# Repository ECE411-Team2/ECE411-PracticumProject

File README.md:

# ECE-411-Team-2

Our project planning will be split into practium checkpoints, each with their own focus:
  1. Teams Formed 
  2. Projects Decided 
  3. Project requirements (Product Design Specification - PDS)
  4. Preliminary schematic
  5. Final schematic + preliminary layout
  6. Boards to manufacturing (actual final schematic + final layout)
  7. Demonstrations

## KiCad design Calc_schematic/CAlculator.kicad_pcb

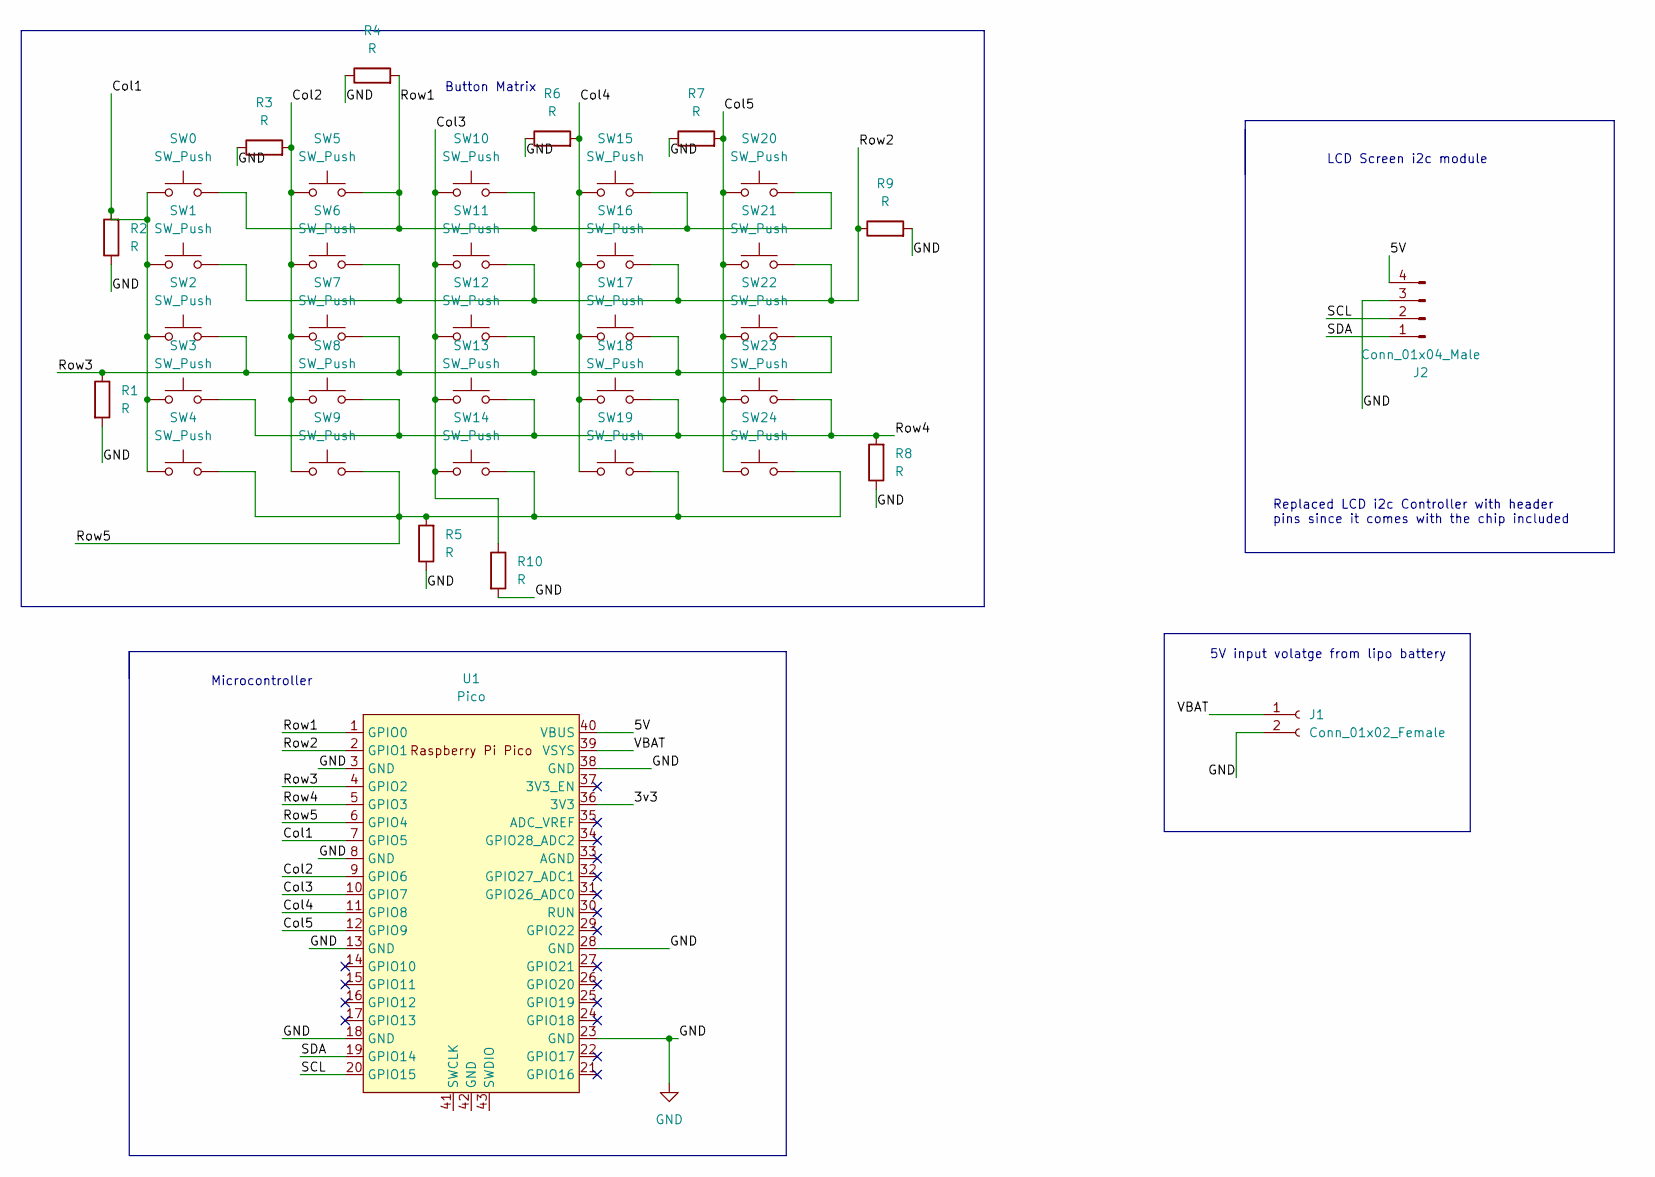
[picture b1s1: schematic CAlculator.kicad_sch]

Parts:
J1: Conn_01x02_Female; JST_PH_B2B-PH-K_1x02_P2.00mm_Vertical
J2: Conn_01x04_Male; PinHeader_1x04_P2.54mm_Vertical
R1, R2, R3, R4, R5, R6, R7, R8, R9, R10: R; RESC3216X60N
SW0, SW1, SW2, SW3, SW4, SW5, SW6, SW7, SW8, SW9, SW10, SW11, SW12, SW13, SW14, SW15, SW16, SW17, SW18, SW19, SW20, SW21, SW22, SW23, SW24: SW_Push; SW_PUSH_6mm_H5mm
U1: Pico; RPi_Pico_SMD_TH

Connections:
/3v3: U1.36 (3V3)
/5V: J2.4, U1.40 (VBUS)
/Col1: R2.2, SW0.1, SW1.1, SW2.1, SW3.1, SW4.1, U1.7 (GPIO5)
/Col2: R3.2, SW5.1, SW6.1, SW7.1, SW8.1, SW9.1, U1.9 (GPIO6)
/Col3: R10.1, SW10.1, SW11.1, SW12.1, SW13.1, SW14.1, U1.10 (GPIO7)
/Col4: R6.2, SW15.1, SW16.1, SW17.1, SW18.1, SW19.1, U1.11 (GPIO8)
/Col5: R7.2, SW20.1, SW21.1, SW22.1, SW23.1, SW24.1, U1.12 (GPIO9)
/Row1: R4.2, SW0.2, SW5.2, SW10.2, SW15.2, SW20.2, U1.1 (GPIO0)
/Row2: R9.1, SW1.2, SW6.2, SW11.2, SW16.2, SW21.2, U1.2 (GPIO1)
/Row3: R1.1, SW2.2, SW7.2, SW12.2, SW17.2, SW22.2, U1.4 (GPIO2)
/Row4: R8.2, SW3.2, SW8.2, SW13.2, SW18.2, SW23.2, U1.5 (GPIO3)
/Row5: R5.2, SW4.2, SW9.2, SW14.2, SW19.2, SW24.2, U1.6 (GPIO4)
/SCL: J2.2, U1.20 (GPIO15)
/SDA: J2.1, U1.19 (GPIO14)
/VBAT: J1.1, U1.39 (VSYS)
GND: J1.2, J2.3, R1.2, R2.1, R3.1, R4.1, R5.1, R6.1, R7.1, R8.1, R9.2, R10.2, U1.3 (GND), U1.8 (GND), U1.13 (GND), U1.18 (GND), U1.23 (GND), U1.28 (GND), U1.38 (GND)

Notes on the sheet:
LCD Screen i2c module
5V input volatge from lipo battery
Microcontroller
Replaced LCD i2c Controller with header pins since it comes with the chip included
Button Matrix

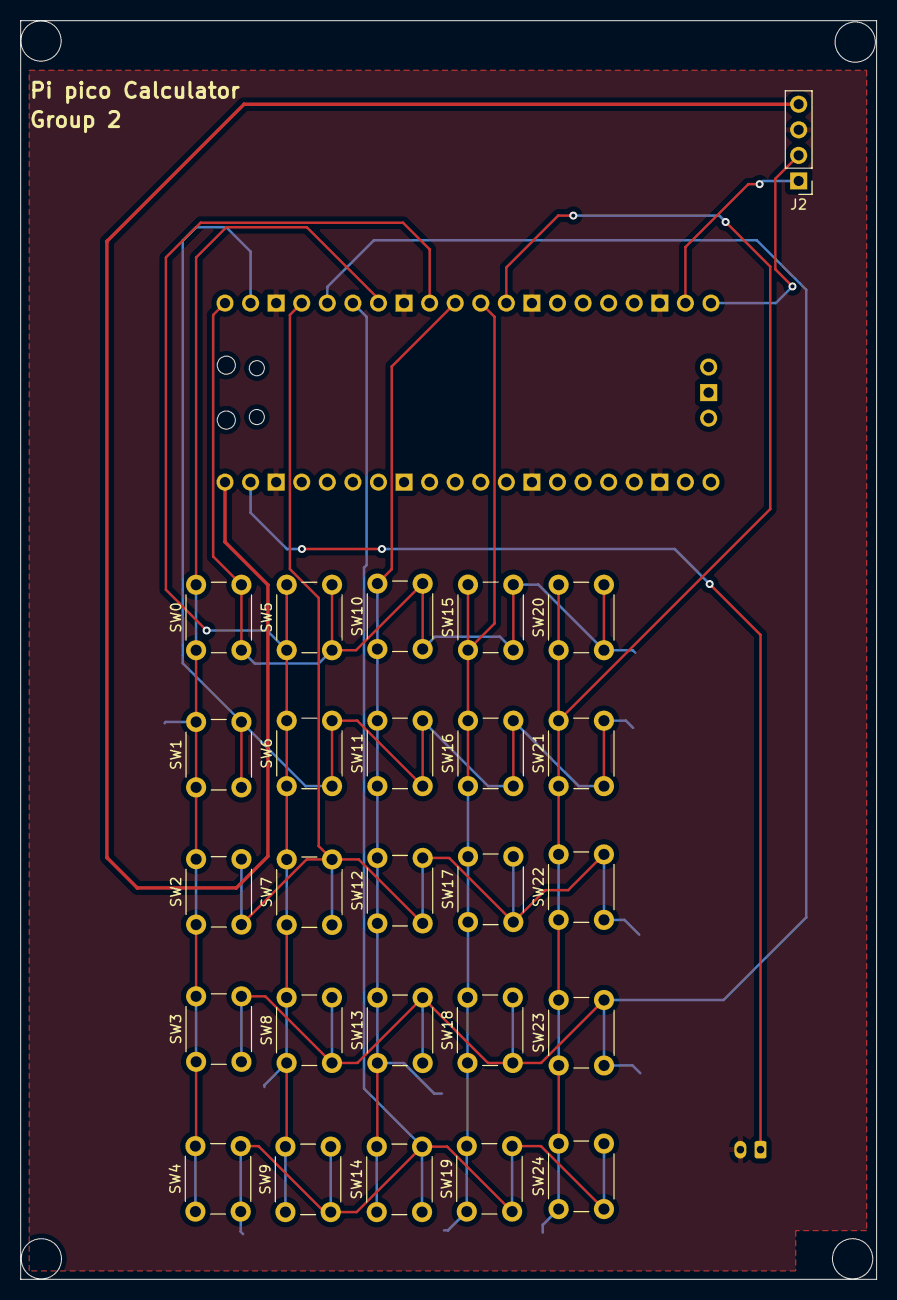
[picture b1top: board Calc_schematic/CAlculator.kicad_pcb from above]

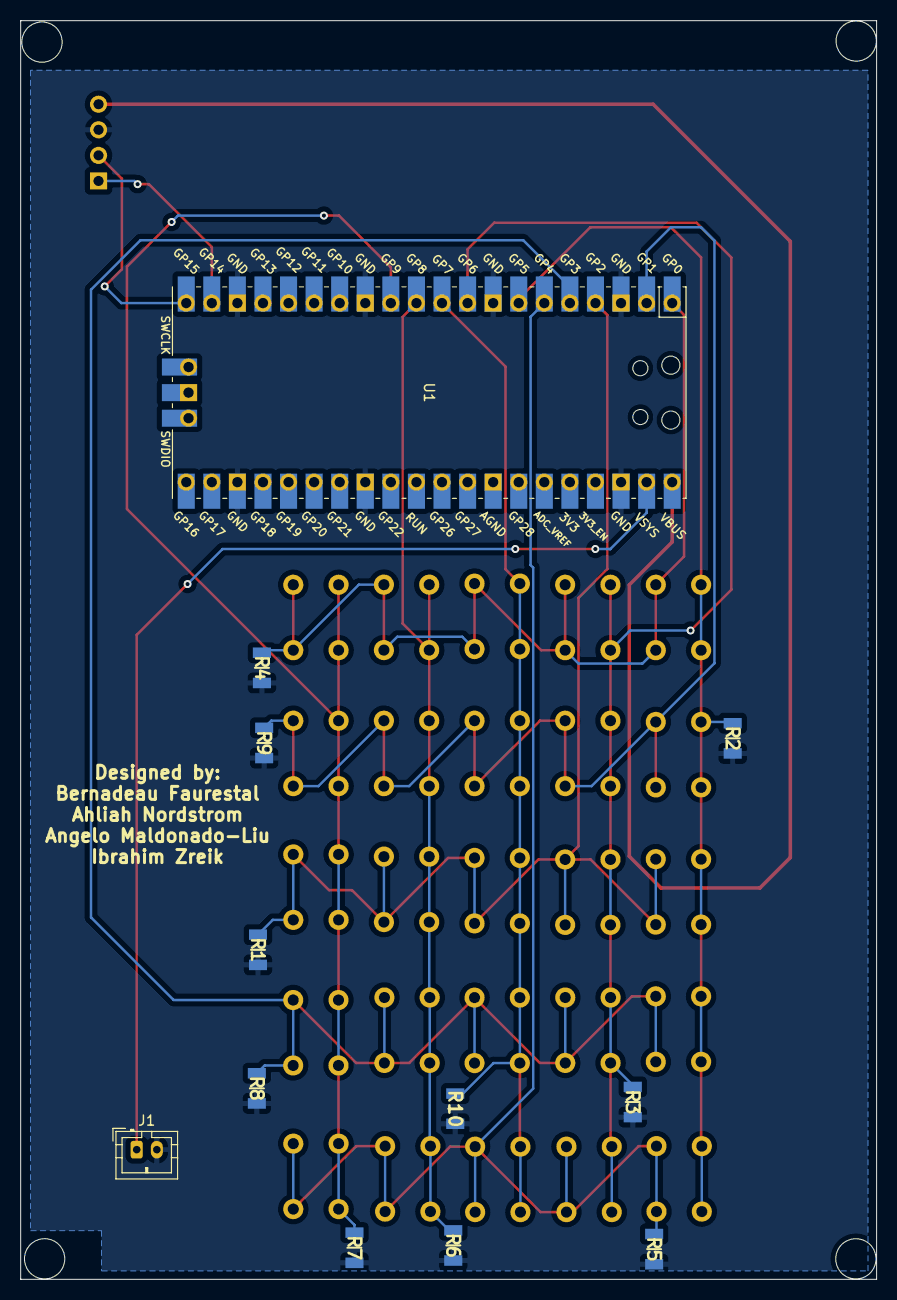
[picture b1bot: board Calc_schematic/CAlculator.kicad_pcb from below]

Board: 2 copper layers, 85.0 x 125.0 mm, 38 parts (12 on the bottom side), 15 nets.

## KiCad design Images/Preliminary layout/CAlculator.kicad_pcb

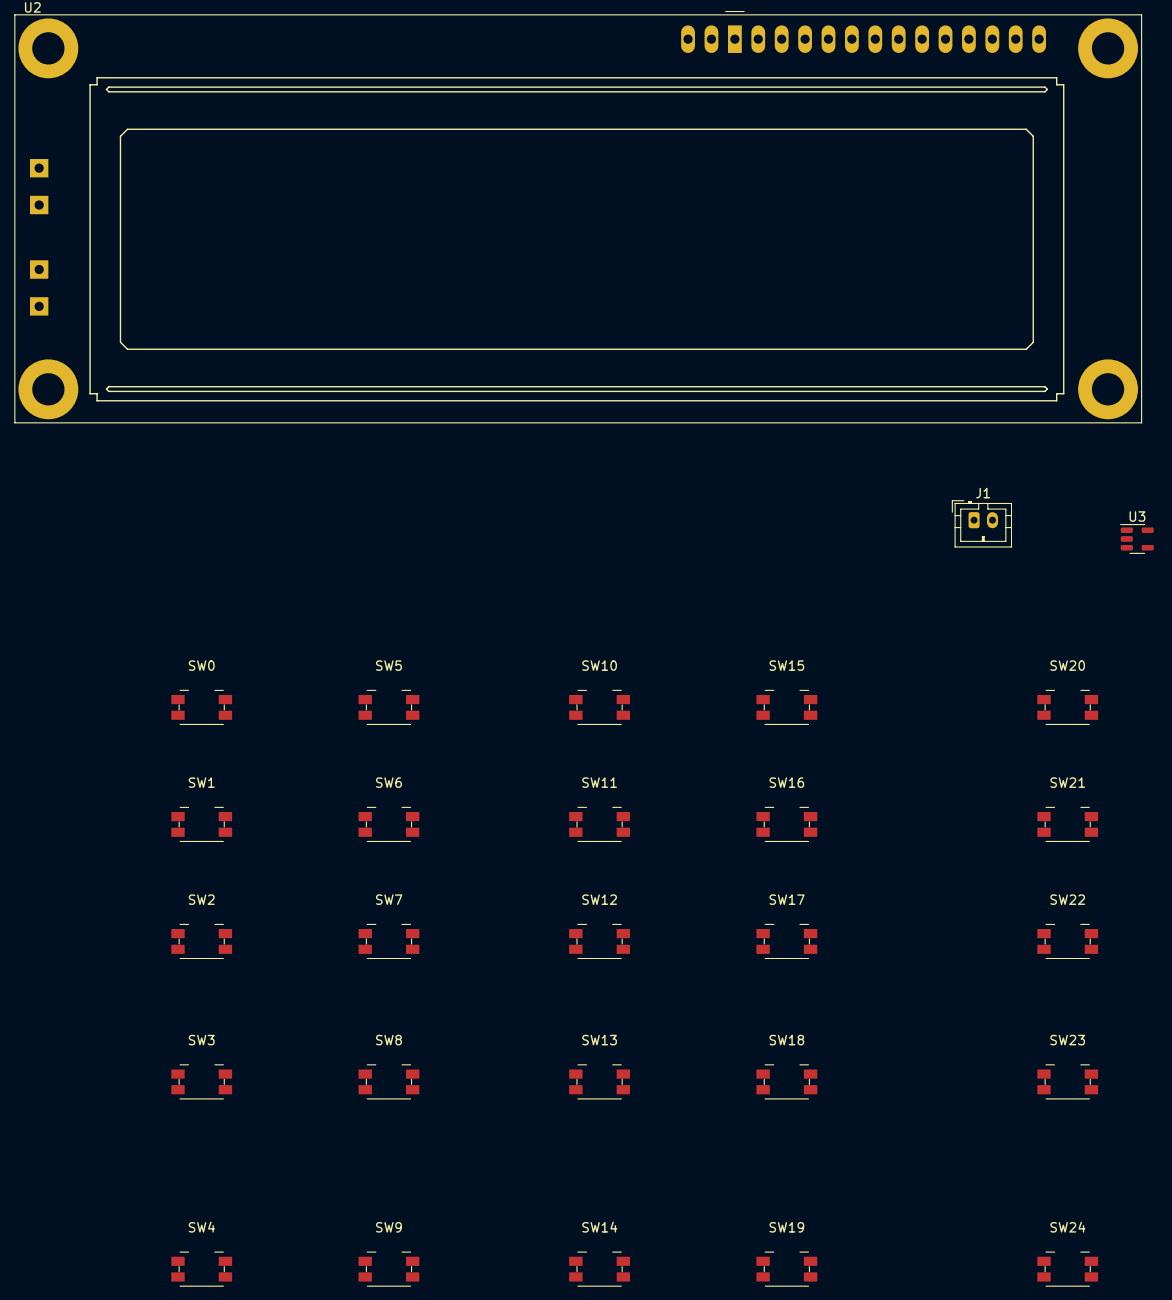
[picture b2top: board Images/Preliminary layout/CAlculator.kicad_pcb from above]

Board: 2 copper layers, 28 parts (0 on the bottom side), 10 nets, no tracks yet.

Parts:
J1: Conn_01x02_Female; JST_PH_B2B-PH-K_1x02_P2.00mm_Vertical
SW0, SW1, SW2, SW3, SW4, SW5, SW6, SW7, SW8, SW9, SW10, SW11, SW12, SW13, SW14, SW15, SW16, SW17, SW18, SW19, SW20, SW21, SW22, SW23, SW24: SW_Push; Panasonic_EVQPUK_EVQPUB
U2: LCD-016N002L
U3: AP2112K-3.3; SOT-23-5

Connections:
unnamed: SW0.1, SW1.1, SW2.1, SW3.1, SW4.1
unnamed: SW0.2, SW5.2, SW10.2, SW15.2, SW20.2
unnamed: SW1.2, SW6.2, SW11.2, SW16.2, SW21.2
unnamed: SW5.1, SW6.1, SW7.1, SW8.1, SW9.1
unnamed: SW10.1, SW11.1, SW12.1, SW13.1, SW14.1
unnamed: SW2.2, SW7.2, SW12.2, SW17.2, SW22.2
unnamed: SW3.2, SW8.2, SW13.2, SW18.2, SW23.2
unnamed: SW4.2, SW9.2, SW14.2, SW19.2, SW24.2
unnamed: SW15.1, SW16.1, SW17.1, SW18.1, SW19.1
unnamed: SW20.1, SW21.1, SW22.1, SW23.1, SW24.1

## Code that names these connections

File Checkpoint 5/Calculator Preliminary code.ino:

//Written by Angelo Maldonado-Liu
//10/28/2022
//PSU ECE 411
//
//
//
/* To do:
      assign values to each row/column pair
      for the equals sign, add in an LCD clear and then output the answer.
      Hex to Binary to Decimal converter.
      need to decide if i have say, 10 in the buffer, when I hit the convert button, does it become 0b1010, and then become 0xA, because if so, then I need to change the size of acceptable values, so that I can fit a D, B, H symbol to signify what type of values we are getting.
      */



#include <Wire.h>
#include <LiquidCrystal_I2C.h>

int row1 = ;
int row2 = ;
int row3 = ;
int row4 = ;
int row5 = ;
int col1 = ;
int col2 = ;
int col3 = ;
int col4 = ;
int col5 = ;

LiquidCrystal_I2C lcd(FIND THE LCD DISPLAY ADDRESS,20,4);  // set the LCD address to blank for a 20 chars and 4 line display (need to determine for our LCD)


char charOutput;
//variables needed for the math, max of 20 digits
char operation = '0';
char value0[18];
char value1[18];
char result[20];
int numType = 0;



int val# = 0;
int numCount;

//trash variable to hold things use with strtoul https://www.tutorialspoint.com/c_standard_library/c_function_strtoul.htm
char *garbage;

void setup() {
  Serial.begin(9600);
  // put your setup code here, to run once:
  //Here we put the button array gpio ports
  lcd.init();                      // initialize the lcd 
  lcd.init();
  // Print a message to the LCD.
  lcd.backlight();
  lcd.setCursor(1,0);




  //variables

}

void loop() {
  // put your main code here, to run repeatedly:
  
  //LCD gpio ports
  pinMode(row1, OUTPUT);
  pinMode(row2, OUTPUT);
  pinMode(row3, OUTPUT);
  pinMode(row4, OUTPUT);
  pinMode(row5, OUTPUT);
  pinMode(col1, INPUT);
  pinMode(col2, INPUT);
  pinMode(col3, INPUT);
  pinMode(col4, INPUT);
  pinMode(col5, INPUT);

  haveInput = 0;
  delay(50);
  if(val# == 1)
  {
    lcd.setCursor(2,1);
  }
  else
  {
    lcd.setCursor(1,0);
  }
  //check which button
  while(haveInput == 0)
  {
    if(digitalRead(col1) == 1)
    {
      //change ROWS and COLUMNS 
      switchIO();

      if(digitalRead(row1) == 1)
      {
        charOutput = ;
      }
      else if(digitalRead(row2) == 1)
      {
        charOutput = ;
      }
      else if(digitalRead(row3) == 1)
      {
        charOutput = ;
      }
      else if(digitalRead(row4) == 1)
      {
        charOutput = ;
      }
      else if(digitalRead(row5) == 1)
      {
        charOutput = ;
      }
      haveInput = 1;
    }
    if(digitalRead(col2) == 1)
    {
      //change ROWS and COLUMNS 
      switchIO();

      if(digitalRead(row1) == 1)
      {
        charOutput = ;
      }
      else if(digitalRead(row2) == 1)
      {
        charOutput = ;
      }
      else if(digitalRead(row3) == 1)
      {
        charOutput = ;
      }
      else if(digitalRead(row4) == 1)
      {
        charOutput = ;
      }
      else if(digitalRead(row5) == 1)
      {
        charOutput = ;
      }
      haveInput = 1;
    }

    if(digitalRead(col3) == 1)
    {
      //change ROWS and COLUMNS 
      switchIO();

      if(digitalRead(row1) == 1)
      {
        charOutput = ;
      }
      else if(digitalRead(row2) == 1)
      {
        charOutput = ;
      }
      else if(digitalRead(row3) == 1)
      {
        charOutput = ;
      }
      else if(digitalRead(row4) == 1)
      {
        charOutput = ;
      }
      else if(digitalRead(row5) == 1)
      {
        charOutput = ;
      }
      haveInput = 1;
    }

    if(digitalRead(col4) == 1)
    {
      //change ROWS and COLUMNS 
      switchIO();

      if(digitalRead(row1) == 1)
      {
        charOutput = ;
      }
      else if(digitalRead(row2) == 1)
      {
        charOutput = ;
      }
      else if(digitalRead(row3) == 1)
      {
        charOutput = ;
      }
      else if(digitalRead(row4) == 1)
      {
        charOutput = ;
      }
      else if(digitalRead(row5) == 1)
      {
        charOutput = ;
      }
      haveInput = 1;
    }

    if(digitalRead(col5) == 1)
    {
      //change ROWS and COLUMNS 
      switchIO();

      if(digitalRead(row1) == 1)
      {
        charOutput = ;
      }
      else if(digitalRead(row2) == 1)
      {
        charOutput = ;
      }
      else if(digitalRead(row3) == 1)
      {
        charOutput = ;
      }
      else if(digitalRead(row4) == 1)
      {
        charOutput = ;
      }
      else if(digitalRead(row5) == 1)
      {
        charOutput = ;
      }
      haveInput = 1;
    }
  }

  //write into the saved number values
  if(operation != '0')
  {
    lcd.setCursor(1,1);
    lcd.print(operation);
    val# = 1;
    return;
  }

  if(numType == 0)
  {
    if(val# == 0)
    {
      value0[numCount] = charOutput;
      numCount++;
      lcd.print(value0);
    }
    else if(val# == 1)
    {
      value1[numCount] = charOutput;
      numCount++;
      lcd.print(value1);
    }
  }
  else if(numType == 1)
  {
    if(val# == 0)
    {
      value0[numCount] = charOutput;
      numCount++;
      lcd.print(value0, BIN);
    }
    else if(val# == 1)
    {
      value1[numCount] = charOutput;
      numCount++;
      lcd.print(value1,BIN);
    }
  }

  else if(numType == 2)
  {
    if(val# == 0)
    {
      value0[numCount] = charOutput;
      numCount++;
      lcd.print(value0, HEX);
    }
    else if(val# == 1)
    {
      value1[numCount] = charOutput;
      numCount++;
      lcd.print(value1, HEX);
    }
  }



  
}

void switchIO() {
  pinMode(row1, INPUT);
  pinMode(row2, INPUT);
  pinMode(row3, INPUT);
  pinMode(row4, INPUT);
  pinMode(row5, INPUT);
  pinMode(col1, OUTPUT);
  pinMode(col2, OUTPUT);
  pinMode(col3, OUTPUT);
  pinMode(col4, OUTPUT);
  pinMode(col5, OUTPUT);
  return;
}

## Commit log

2022-10-07 Create Idea Brainstorm
2022-10-07 Create (PDS) Product Design Specification
2022-10-07 Create BOM v1
2022-10-07 Create Schematic v1
2022-10-07 Rename Checkpoint 1-3/BOM v1 to Checkpoint 4/BOM v1
2022-10-07 Create Schematic v2
2022-10-07 Create Prototyping Log
    Update log as you go
2022-10-07 Create Parts Ordered
2022-10-07 Rename Checkpoint 4/Schematic v2 to Checkpoint 5/Schematic v2
2022-10-07 Rename Checkpoint 1-3/Schematic v1 to Checkpoint 4/Schematic v1
2022-10-07 Create Research Log & Links
2022-10-07 Rename Schematic v2 to Final Schematic
2022-10-07 Rename Schematic v1 to Preliminary Schematic
2022-10-07 Create Preliminary Layout
2022-10-07 Update Preliminary Layout
2022-10-07 Create Final Layout
2022-10-07 Create Actual Final Schematic
2022-10-07 Create Rough Schematic
2022-10-07 Create Block Diagram
2022-10-07 Create Initial Timeline
2022-10-07 Create Final Timeline
2022-10-11 Create Team Member Info
2022-10-11 Update Team Member Info
2022-10-11 Update and rename .gitkeep to README
2022-10-11 Rename Checkpoint 5/Parts Ordered to Checkpoint 4/Parts Ordered
2022-10-11 Rename .gitkeep to README
2022-10-28 Add files via upload
    This is the preliminary code for the calculator
2022-10-31 Update Parts Ordered
2022-10-31 Update Prototyping Log
2022-11-03 prototype
2022-11-03 schematic update
2022-11-03 last mod
2022-11-10 changed delay
2022-11-10 updated delay and transmissions
2022-11-10 updated i2c controller
2022-11-10 most pins connected except Vbus and ground
    Going to use ground plane so no need to connect ground pins yet
2022-11-11 Add files via upload
    Preliminary C code, as we are switching over to C
2022-11-17 final CAD
    board sent to FaB
2022-11-18 Rename calculator prototype code.ino to calculator prototyping code.ino
2022-11-27 change i2c default pins
    change the i2c pins from default values to GP14 and GP15
